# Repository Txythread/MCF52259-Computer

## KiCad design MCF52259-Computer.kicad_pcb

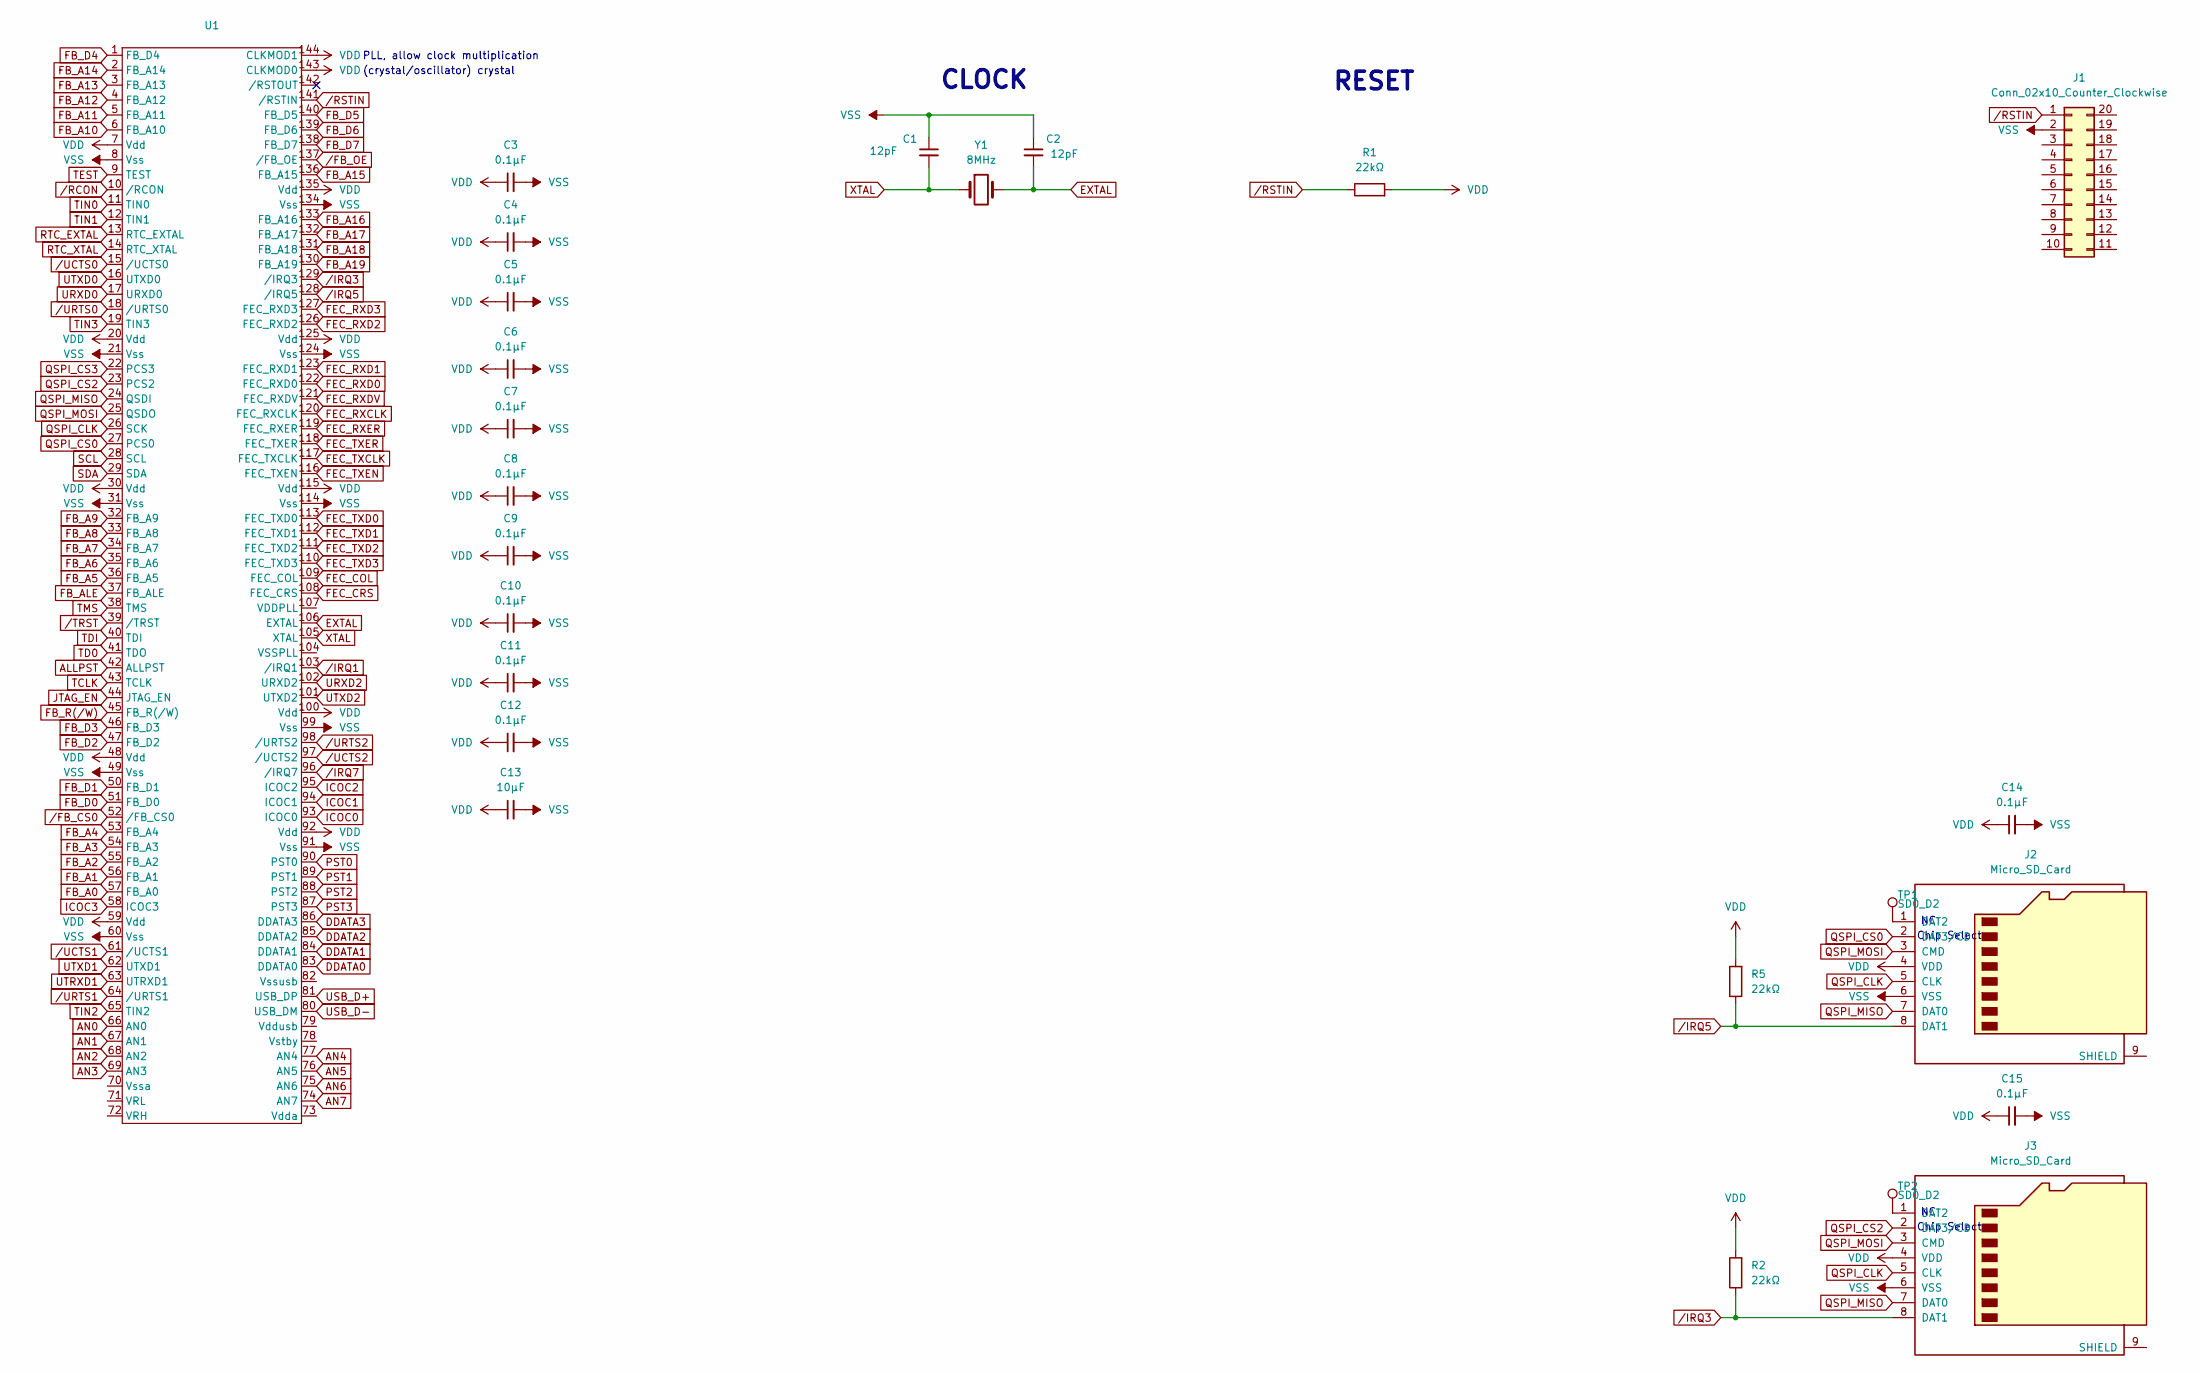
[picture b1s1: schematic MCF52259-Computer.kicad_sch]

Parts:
C1, C2: 12pF; C_0603_1608Metric_Pad1.08x0.95mm_HandSolder
C3, C4, C5, C6, C7, C8, C9, C10, C11, C12, C14, C15: 0.1µF; C_0805_2012Metric_Pad1.18x1.45mm_HandSolder
C13: 10µF; C_0603_1608Metric_Pad1.08x0.95mm_HandSolder
J1: Conn_02x10_Counter_Clockwise; PinHeader_2x10_P2.54mm_Vertical
J2, J3: Micro_SD_Card; microSD_HC_Wuerth_693072010801
R1, R2, R5: 22kΩ; R_0805_2012Metric_Pad1.20x1.40mm_HandSolder
TP1, TP2: SD0_D2; TestPoint_Pad_D1.0mm
U1: LQFP-144_20x20mm_P0.5mm
Y1: 8MHz; Crystal_SMD_Abracon_ABM3-2Pin_5.0x3.2mm_HandSoldering

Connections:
ALLPST: U1.42 (ALLPST)
AN0: U1.66 (AN0)
AN1: U1.67 (AN1)
AN2: U1.68 (AN2)
AN3: U1.69 (AN3)
AN4: U1.77 (AN4)
AN5: U1.76 (AN5)
AN6: U1.75 (AN6)
AN7: U1.74 (AN7)
DDATA0: U1.83 (DDATA0)
DDATA1: U1.84 (DDATA1)
DDATA2: U1.85 (DDATA2)
DDATA3: U1.86 (DDATA3)
EXTAL: C2.2, U1.106 (EXTAL), Y1.2
FB_A0: U1.57 (FB_A0)
FB_A1: U1.56 (FB_A1)
FB_A2: U1.55 (FB_A2)
FB_A3: U1.54 (FB_A3)
FB_A4: U1.53 (FB_A4)
FB_A5: U1.36 (FB_A5)
FB_A6: U1.35 (FB_A6)
FB_A7: U1.34 (FB_A7)
FB_A8: U1.33 (FB_A8)
FB_A9: U1.32 (FB_A9)
FB_A10: U1.6 (FB_A10)
FB_A11: U1.5 (FB_A11)
FB_A12: U1.4 (FB_A12)
FB_A13: U1.3 (FB_A13)
FB_A14: U1.2 (FB_A14)
FB_A15: U1.136 (FB_A15)
FB_A16: U1.133 (FB_A16)
FB_A17: U1.132 (FB_A17)
FB_A18: U1.131 (FB_A18)
FB_A19: U1.130 (FB_A19)
FB_ALE: U1.37 (FB_ALE)
FB_D0: U1.51 (FB_D0)
FB_D1: U1.50 (FB_D1)
FB_D2: U1.47 (FB_D2)
FB_D3: U1.46 (FB_D3)
FB_D4: U1.1 (FB_D4)
FB_D5: U1.140 (FB_D5)
FB_D6: U1.139 (FB_D6)
FB_D7: U1.138 (FB_D7)
FB_R(/W): U1.45 (FB_R(/W))
FEC_COL: U1.109 (FEC_COL)
FEC_CRS: U1.108 (FEC_CRS)
FEC_RXCLK: U1.120 (FEC_RXCLK)
FEC_RXD0: U1.122 (FEC_RXD0)
FEC_RXD1: U1.123 (FEC_RXD1)
FEC_RXD2: U1.126 (FEC_RXD2)
FEC_RXD3: U1.127 (FEC_RXD3)
FEC_RXDV: U1.121 (FEC_RXDV)
FEC_RXER: U1.119 (FEC_RXER)
FEC_TXCLK: U1.117 (FEC_TXCLK)
FEC_TXD0: U1.113 (FEC_TXD0)
FEC_TXD1: U1.112 (FEC_TXD1)
FEC_TXD2: U1.111 (FEC_TXD2)
FEC_TXD3: U1.110 (FEC_TXD3)
FEC_TXEN: U1.116 (FEC_TXEN)
FEC_TXER: U1.118 (FEC_TXER)
ICOC0: U1.93 (ICOC0)
ICOC1: U1.94 (ICOC1)
ICOC2: U1.95 (ICOC2)
ICOC3: U1.58 (ICOC3)
JTAG_EN: U1.44 (JTAG_EN)
unnamed: J2.1 (DAT2), TP1.1
unnamed: J3.1 (DAT2), TP2.1
PST0: U1.90 (PST0)
PST1: U1.89 (PST1)
PST2: U1.88 (PST2)
PST3: U1.87 (PST3)
QSPI_CLK: J2.5 (CLK), J3.5 (CLK), U1.26 (SCK)
QSPI_CS0: J2.2 (DAT3/CD), U1.27 (PCS0)
QSPI_CS2: J3.2 (DAT3/CD), U1.23 (PCS2)
QSPI_CS3: U1.22 (PCS3)
QSPI_MISO: J2.7 (DAT0), J3.7 (DAT0), U1.24 (QSDI)
QSPI_MOSI: J2.3 (CMD), J3.3 (CMD), U1.25 (QSDO)
RTC_EXTAL: U1.13 (RTC_EXTAL)
RTC_XTAL: U1.14 (RTC_XTAL)
SCL: U1.28 (SCL)
SDA: U1.29 (SDA)
TCLK: U1.43 (TCLK)
TD0: U1.41 (TDO)
TDI: U1.40 (TDI)
TEST: U1.9 (TEST)
TIN0: U1.11 (TIN0)
TIN1: U1.12 (TIN1)
TIN2: U1.65 (TIN2)
TIN3: U1.19 (TIN3)
TMS: U1.38 (TMS)
URXD0: U1.17 (URXD0)
URXD2: U1.102 (URXD2)
USB_D+: U1.81 (USB_DP)
USB_D-: U1.80 (USB_DM)
UTRXD1: U1.63 (UTRXD1)
UTXD0: U1.16 (UTXD0)
UTXD1: U1.62 (UTXD1)
UTXD2: U1.101 (UTXD2)
VDD: C3.1, C4.1, C5.1, C6.1, C7.1, C8.1, C9.1, C10.1, C11.1, C12.1, C13.1, C14.1, C15.1, J2.4 (VDD), J3.4 (VDD), R1.2, R2.2, R5.2, U1.7 (Vdd), U1.20 (Vdd), U1.30 (Vdd), U1.48 (Vdd), U1.59 (Vdd), U1.92 (Vdd), U1.100 (Vdd), U1.115 (Vdd), U1.125 (Vdd), U1.135 (Vdd), U1.143 (CLKMOD0), U1.144 (CLKMOD1)
VSS: C1.1, C2.1, C3.2, C4.2, C5.2, C6.2, C7.2, C8.2, C9.2, C10.2, C11.2, C12.2, C13.2, C14.2, C15.2, J1.2, J2.6 (VSS), J3.6 (VSS), U1.8 (Vss), U1.21 (Vss), U1.31 (Vss), U1.49 (Vss), U1.60 (Vss), U1.91 (Vss), U1.99 (Vss), U1.114 (Vss), U1.124 (Vss), U1.134 (Vss)
XTAL: C1.2, U1.105 (XTAL), Y1.1
/FB_CS0: U1.52 (/FB_CS0)
/FB_OE: U1.137 (/FB_OE)
/IRQ1: U1.103 (/IRQ1)
/IRQ3: J3.8 (DAT1), R2.1, U1.129 (/IRQ3)
/IRQ5: J2.8 (DAT1), R5.1, U1.128 (/IRQ5)
/IRQ7: U1.96 (/IRQ7)
/RCON: U1.10 (/RCON)
/RSTIN: J1.1, R1.1, U1.141 (/RSTIN)
/TRST: U1.39 (/TRST)
/UCTS0: U1.15 (/UCTS0)
/UCTS1: U1.61 (/UCTS1)
/UCTS2: U1.97 (/UCTS2)
/URTS0: U1.18 (/URTS0)
/URTS1: U1.64 (/URTS1)
/URTS2: U1.98 (/URTS2)

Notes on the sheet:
CLOCK
Chip Select
(crystal/oscillator) crystal
PLL, allow clock multiplication
RESET

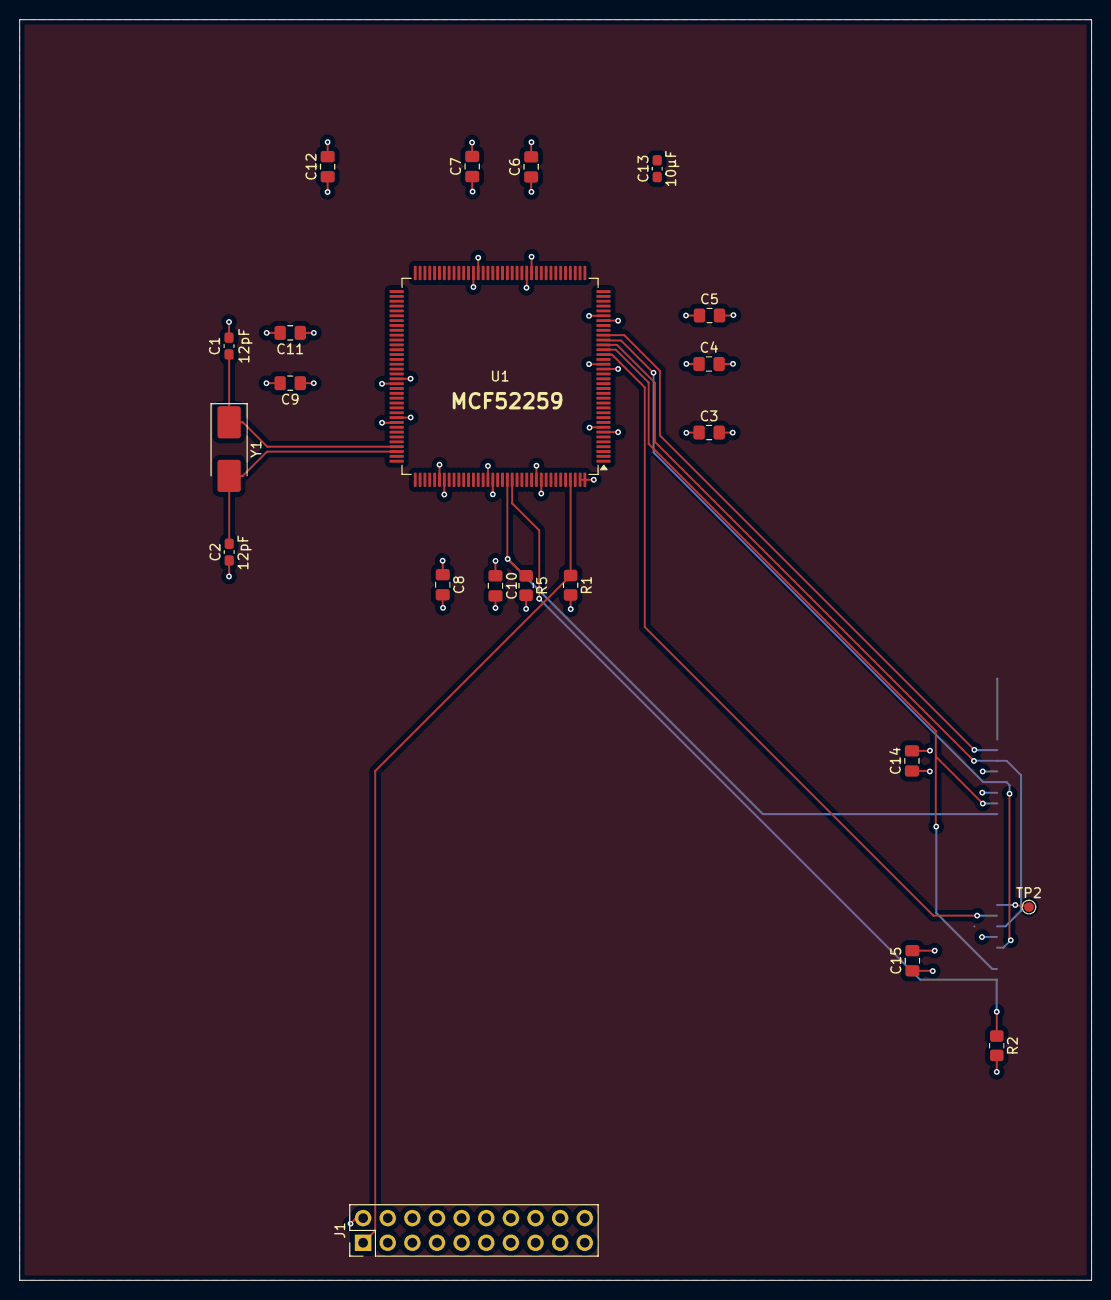
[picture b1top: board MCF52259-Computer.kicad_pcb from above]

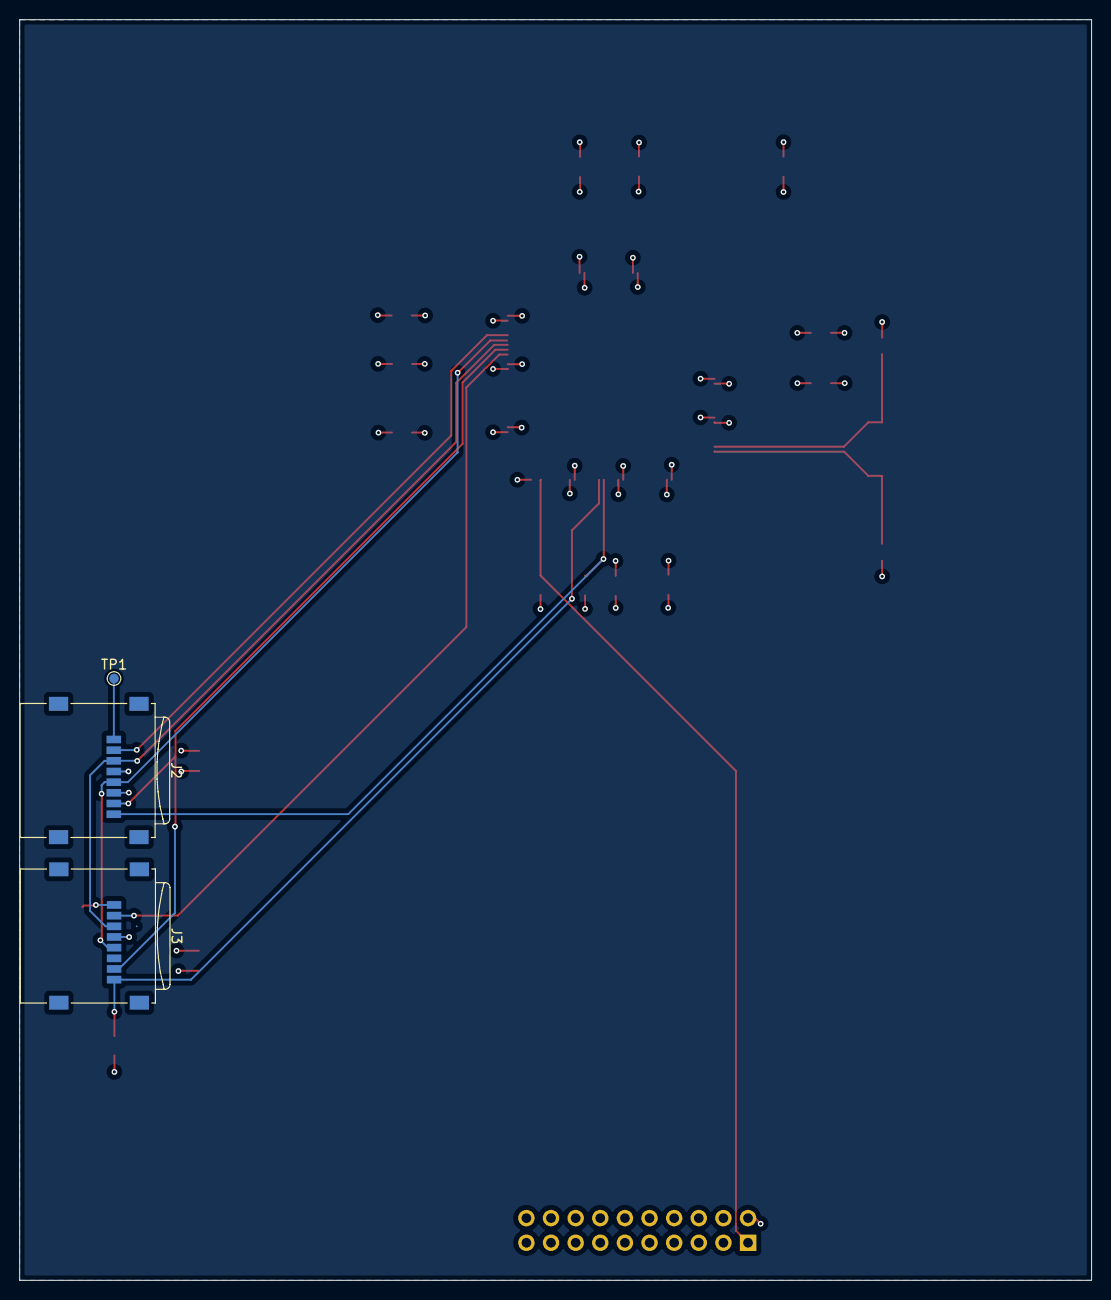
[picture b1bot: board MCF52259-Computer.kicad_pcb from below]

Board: 6 copper layers, 110.5 x 130.0 mm, 25 parts (3 on the bottom side), 14 nets.

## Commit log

2025-11-21 Configured Clock Modes Correctly
2025-11-22 Added .gitignore
2025-11-22 Added Reset Circuitry
2025-11-22 Added Decoupling Caps
2025-11-23 Added SD-Card
2025-11-23 Added Second Micro SD-Card
2025-11-23 Added Neccesary Pull-Up to IRQ3
